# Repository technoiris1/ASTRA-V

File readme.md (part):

# ASTRA-V

heyo! Manan this side - this is my second big hardware project after my foldable 3d printer - ASTRA-V. Stands for Autonomous Stabilised Thrust Recovery Ascent Vehicle.<br>

The concept is simple - Go up - attain free fall - thrust again a lil when around 3 feet from the ground - land.

Its using LiDars to calculate the height precisely and they are pretty quick, so no problems.

First iteration -
This very iteration of ASTRA-V has the following tasks - going up 15 feet, attaining a proper stable freefall and then land. Now the word *land* is the main thing, so like this is what the hardest part is - so lets discuss the whole thing step by step.

## Launch
### Trigger
We are using a RF module to trigger the launch, it is in the flight controller.
### Process
The Servo motor will be kicked by the flight controller - which will open the flow of the O2 into the Acrylic Rod Chamber(We will come to the fuel part later on), and along with the servo - an arc ignitor will also be kicked which will burn the fuel. *sshhhhhhhhhhiiiiiiiiuuuuuuuuu* and with that the burnt fuel gases will come out pressurized of the nozzle and *shrrrooooommmm* the rockets up - it will go up 30 feet in this iteration.

## Free fall
Pretty simple, once reached the desired height(30 feet here) the valve will be kicked to close. Thus no oxidiser - thus no thrust and no more going up. Then it will just fall down - tearing down the vigilantly through the air.

## Landing
Now this is the special sauce, the complex thing - in simple words - LiDar sensors are highly sensitive sensors which mainly work on lasers so really quick. They will be sensing the altitude and sending it to the flight computer, now as soon as the altitude or around 15 feet (in this case) is reached - the computer will kick up the servo and ignitor once again to push enough thrust to neutralise the G force attained in the freefall. So like - the whole rocket will have a gentle touchdown in the air using thrusters. Now along with the engine mechanism, one more thing kicked would be the servo motors to deploy the landing legs - they have a really wide span as you can see in the images - so it gonna land really well.

## Flight Controller
Flight controller is a custom made from scratch which uses Pi pico as the main board. It uses MPU-6050 as the Gyro and BMP-280 as the altimeter as its a barometer. It has pins for breakouts of all these things along with connections with landing servos, LiDar sensors, Fuel Servos and the Arc Ignitor. It has 7 motor connections, 2 LiDar, 1 for MPU6050 and BMP280 each, it has different capacitors placed overall for fluctuations etc.

## Fuel
It is using Acrylic as a fuel along with O2 as the oxidiser. Pretty simple there is a chamber with acrylic rod and a servo controlled apparatus for the input of oxygen into the chamber. So the burnt O2 will heat up and burn the Acrylic rod, thus the Acrylic vapours will move out really really quickly off the nozzle providing thrust.

## Rocket motor and thrust vectoring
I am working on a basic servo controlled thrust vectoring system to control the direction of the thrust. This will allow for more precise control of the rocket's trajectory. The servos will be fitted on two different rings, one ring with a servo will be connected to the tube body of rocket and it will rotate another ring inside it, which is housing another servo and that servo will be connected to a ring joint to the rocket motor. So in this way there will be a whole 2-axis thrust vectoring system. I am currently working on the design and 3d model, will put here as soon as i'm done.

## Why am I making this thing?
cuz am crazy

## BOM
| ASTRA-V        | 1                                                                                                                                              | 2   |  3   | 4      |  5      |  6                                                                                                                                                                                                                                                                                                                                                                                                                                                                                                                                                                                                                                                                                                   |
|:----------------------|:--------------------------------------------------------------------------------------------------------------------------------------------------------|:-------------|:-------------|:----------------|:----------------|:-------------------------------------------------------------------------------------------------------------------------------------------------------------------------------------------------------------------------------------------------------------------------------------------------------------------------------------------------------------------------------------------------------------------------------------------------------------------------------------------------------------------------------------------------------------------------------------------------------------------------------------------------------------------------------------------------------------|
| ASTRA                 | Autonomous Stabilised Thrust Recovery Ascent                                                                                                            |              |              |                 |                 |                                                                                                                                                                                                                                                                                                                                                                                                                                                                                                                                                                                                                                                                                                              |
|                       |                                                                                                                                                         |              |              |                 |                 |                                                                                                                                                                                                                                                                                                                                                                                                                                                                                                                                                                                                                                                                                                              |
| BOM-                  |                                                                                                                                                         |              |              |                 |                 |                                                                                                                                                                                                                                                                                                                                                                                                                                                                                                                                                                                                                                                                                                              |
| Name                  | Use case                                                                                                                                                | price each   | units        | total price inr | total price usd | link                                                                                                                                                                                                                                                                                                                                                                                                                                                                                                                                                                                                                                                                                                         |
| MG946R servo motors   | Landing legs deployment                                                                                                                                 | 800          | 4            | 3200            | 37              | https://thinkrobotics.com/products/standard-metal-servo-mg946r-1?variant=12765401514056                                                                                                                                                                                                                                                                                                                                                                                                                                                                                                                                                                                                                      |
| LiDar sensor          | to measure height quickly                                                                                                                               | 2500         | 2            | 5000            | 57              | https://thinkrobotics.com/products/tf-luna-lidar-tof-distance-ranging-sensor-8m                                                                                                                                                                                                                                                                                                                                                                                                                                                                                                                                                                                                                              |
| Raspberry pi pico W   | the main controller of the flight                                                                                                                       | 700          | 2            | 1400            | 16              | https://thinkrobotics.com/products/raspberry-pi-pico-w-online?variant=44615124386109                                                                                                                                                                                                                                                                                                                                                                                                                                                                                                                                                                                                                         |
| BMP280 breakout       | the altimeter of the flight ctrl                                                                                                                        | 70           | 2            | 140             | 2               | https://thinkrobotics.com/products/bmp280-barometric-sensor-module-3-3v-5v?variant=32045116325974                                                                                                                                                                                                                                                                                                                                                                                                                                                                                                                                                                                                            |
| MPU 6050              | gyro sensor                                                                                                                                             | 300          | 2            | 600             | 7               | https://thinkrobotics.com/products/mpu6050-gyroscope-sensor?variant=16158094786632                                                                                                                                                                                                                                                                                                                                                                                                                                                                                                                                                                                                                           |
| nrf module            | trigger for rocket to go boom                                                                                                                           | 80           | 2            | 160             | 2               | https://roboticsdna.in/product/nrflongrenge24l01/                                                                                                                                                                                                                                                                                                                                                                                                                                                                                                                                                                                                                                                            |
| pin headers           | pin headers on pcb                                                                                                                                      | 11.5         | 20           | 250             | 3               | https://thinkrobotics.com/products/single-row-2-54-mm-pitch-header-40-pin?variant=12744266055752                                                                                                                                                                                                                                                                                                                                                                                                                                                                                                                                                                                                             |
| battery               | battery                                                                                                                                                 | 1900         | 1            | 1900            | 22              | https://robocraze.com/products/bonka-2200mah-35c-3s1p-11-1v-lipo-battey?_pos=1&_sid=bea5fbb80&_ss=r                                                                                                                                                                                                                                                                                                                                                                                                                                                                                                                                                                                                          |
| battery charger       | battery charger                                                                                                                                         | 350          | 1            | 350             | 4               | https://robocraze.com/products/b3-pro-li-po-battery-charger?_pos=2&_sid=bea5fbb80&_ss=r                                                                                                                                                                                                                                                                                                                                                                                                                                                                                                                                                                                                                      |
| 12v to 5v stepdown    | as the name suggests, its the best i could find right now as i need >15A to feed to all the servos and lidars and all, gonna use a simpler one if found | 1300         | 1            | 1300            | 15              | https://www.amazon.in/Regulator-Converter-Step-Down-Waterproof-Transformer/dp/B0BB7TNNR9/ref=sr_1_2?adgrpid=152001381314&dib=eyJ2IjoiMSJ9.7LdIaw4uy4t_ud4_Gg2x1FYfv0hCAr6r5n_X9XjOV1DIgPk0lzrRwCeS5vQJs9ifIwk5jeHmpClpv-KxfE_R6W-4eQ8La3mx5k82_zUEXtoWDIm8fWkmIPpgv6_Jc1wZnojyiQzVQ-MZeZGr-iGJw1jx3eatirHtnHmqE5kdzw5dZ7hAgFZO8xEtYhY6lZw5g143_Y3Bxg3XxFJVMQ1qbN5F_TIHW0vvLTUpqolevq4.H1BIrdzZZDv5Qg4POX_tB1USdrkHpUucbGJxVSRyHRA&dib_tag=se&ext_vrnc=hi&hvadid=658161935919&hvdev=c&hvlocphy=9061777&hvnetw=g&hvqmt=e&hvrand=16993244603842095821&hvtargid=kwd-332476321330&hydadcr=18599_2250683&keywords=12v%2Bto%2B5v%2Bconverter%2B10a&mcid=59e334a8862a3bdfa27f93f5b047b91e&qid=1757371930&sr=8-2&th=1 |
| 0.1uf ceramic cap     | on pcb                                                                                                                                                  | 5            | 3            | 15              | 1               | https://quartzcomponents.com/products/10000-pf-0-1uf-ceramic-capacitor?_pos=1&_sid=c9f6e0456&_ss=r                                                                                                                                                                                                                                                                                                                                                                                                                                                                                                                                                                                                           |
| 470uf cap             | on pcb                                                                                                                                                  | 7            | 3            | 21              | 1               | https://quartzcomponents.com/products/470uf-50v-electrolytic-capacitor?_pos=1&_sid=1ae57eeec&_ss=r                                                                                                                                                                                                                                                                                                                                                                                                                                                                                                                                                                                                           |
| 100uf cap             | on pcb                                                                                                                                                  | 3            | 10           | 30              | 1               | https://quartzcomponents.com/products/100%CE%BCf-35v-radial-electrolytic-capacitor?_pos=3&_sid=f5c2847a1&_ss=r                                                                                                                                                                                                                                                                                                                                                                                                                                                                                                                                                                                               |
| 10uf cap              | on pcb                                                                                                                                                  | 3            | 10           | 30              | 1               | https://quartzcomponents.com/products/10uf-50v-electrolytic-capacitor?_pos=2&_sid=5efdc15a5&_ss=r                                                                                                                                                                                                                                                                                                                                                                                                                                                                                                                                                                                                            |
| push button           | to be on the fire remote and some other usecases like replacing the arc ignitor small button with large ones to make it easier to work with             | 20           | 3            | 60              | 1               | https://thinkrobotics.com/products/6mm-tactile-push-button-pack-of-20?variant=33484370313302                                                                                                                                                                                                                                                                                                                                                                                                                                                                                                                                                                                                                 |
| arc igniter           | lighter for the fuel etc.                                                                                                                               | 150          | 2            | 300             | 4               | https://quartzcomponents.com/products/arc-cigarette-lighter-parts-diy-electronic-lighter-kit?variant=35137047789721&country=IN&currency=INR&utm_medium=product_sync&utm_source=google&utm_content=sag_organic&utm_campaign=sag_organic?utm_source=google&utm_medium=FreeListings&gad_source=1&gad_campaignid=20393598841&gbraid=0AAAAACPPFdPr-dR7QR1-p34kLl_MJcUyZ&gclid=CjwKCAjw2vTFBhAuEiwAFaScwrnDlRlH-qV1CVbSip1f13rZR5dapHQqdkiod5_ZJnDHndvW4T8w7hoCpK8QAvD_BwE                                                                                                                                                                                                                                         |
| 18650 li-on battery   | battery for the arc igniter                                                                                                                             | 100          | 2            | 200             | 3               |                                                                                                                                                                                                                                                                                                                                                                                                                                                                                                                                                                                                                                                                                                              |
| 18650 battery charger | charger for the battery                                                                                                                                 | 100          | 1            | 100             | 2               | https://quartzcomponents.com/products/18650-li-ion-battery-charger-for-single-cell?_pos=2&_sid=500a0bb39&_ss=r                                                                                                                                                                                                                                                                                                                                                                                                                                                                                                                                                                                               |
| 18650 battery holder  | holder for the battery                                                                                                                                  | 25           | 1            | 25              | 1               | https://quartzcomponents.com/products/single-cell-18650-li-ion-battery-holder?_pos=1&_sid=1d517396f&_ss=r                                                                                                                                                                                                                                                                                                                                                                                                                                                                                                                                                                                                    |
| flight controller PCB | main board                                                                                                                                              | 5000         | 1            | 5000            | 57              | https://github.com/Manan-Coder/ASTRA-V/tree/main/Flight%20Controller                                                                                                                                                                                                                                                                                                                                                                                                                                                                                                                                                                                                                                         |
| cardboard tube        | for the main tube, it will be having the glass cloth on it                                                                                              | 675          | 1            | 675             | 8               | https://www.amazon.in/Inches-Mailing-Tubes-Metal-Length/dp/B0CPWVSQKS/ref=sxin_15_pa_sp_search_thematic_sspa?content-id=amzn1.sym.739e670d-dfb3-4be0-9815-d8c5c0372e07%3Aamzn1.sym.739e670d-dfb3-4be0-9815-d8c5c0372e07&crid=2GBA8S78DLCM5&cv_ct_cx=cardboard%2Btube%2B4%22&keywords=cardboard%2Btube%2B4%22&pd_rd_i=B0CPWWGCS6&pd_rd_r=d6a15d33-a3c1-48d5-9d6b-41144c98fbc2&pd_rd_w=gimTs&pd_rd_wg=ga18o&pf_rd_p=739e670d-dfb3-4be0-9815-d8c5c0372e07&pf_rd_r=P861P04YA3F2CMA1501D&qid=1757196703&sbo=RZvfv%2F%2FHxDF%2BO5021pAnSA%3D%3D&sprefix=cardboard%2Btube%2B4%2Caps%2C326&sr=1-5-66673dcf-083f-43ba-b782-d4a436cc5cfb-spons&sp_csd=d2lkZ2V0TmFtZT1zcF9zZWFyY2hfdGhlbWF0aWM&th=1                     |
| fibre glass cloth     | to make the main tube and make it durable                                                                                                               | 650          | 1            | 650             | 8               | https://www.amazon.in/Fiber-Glass-Cloth-Thickness-10/dp/B0CX1W4TBQ/ref=sr_1_9?crid=1LLKHFYFT24HK&dib=eyJ2IjoiMSJ9.MnhabvxjPrKqUa-3qfa9HY03oFXYKF32Fj4yScgtEWZmGd4QetX8xCNmP-U4g03CMz332kFSD_Zr26WBeGN7ZlPdfwIAevGNnYGiaCj0NQtCt4dzZedN31q90f6f_DtvvAzWLvAysMYQN5fd6bhTNXrjic6mWXOIXJJkzA1OrG0wGstpOiyJcR-gjvNRUQdOQDPHR4tG6MCcP1jrJ2SmAj6i-Q2AUSvXU3IjdhgtvNQo_Au578cT7GSHlRpyLHSAwl6DbeVC0NJLR6-jL2DYqQsgoUJnBfwzdOTwIzhMt-U.9NS5zXLIkieWGsWLpckPP25cPN2hKeon7ZWg-9ju_l8&dib_tag=se&keywords=fibre+glass+cloth&qid=1757106200&sprefix=fibre+glass+clot%2Caps%2C308&sr=8-9                                                                                                                                   |
| epoxy resin           | to stick the glass cloth to the main tube                                                                                                               | 500          | 1            | 500             | 6               | https://www.amazon.in/gp/product/B0F5W94NLF/ref=ewc_pr_img_1?th=1                                                                                                                                                                                                                                                                                                                                                                                                                                                                                                                                                                                                                                            |
| Carbon Fibre rods     | Landing legs                                                                                                                                            | 140          | 12           | 1680            | 20              | https://thinkrobotics.com/products/carbon-fiber-solid-tube-1-m?variant=39329659650134                                                                                                                                                                                                                                                                                                                                                                                                                                                                                                                                                                                                                        |
| oxygen can            | oxidiser for fuel                                                                                                                                       | 1300         | 1            | 1300            | 15              | https://www.amazon.in/breathing-difficulties-Respiration-Lightweight-Travel-Friendly/dp/B0DNXRSX7V/ref=sr_1_5?crid=1GLANMNZO4DFP&dib=eyJ2IjoiMSJ9.2r-hUIMRfcgu623xclaCpK_-iEC730gRlXmkWliNUGdt0qy5bULYgXonakf4B36Uh0WasSftxzVFPrNAktj2EVcn-2fMG8zpUV9mtXioBG0G9hnYFOc7-LZp1YGxAK6olLUZcGkyajMMYhokfJNw9zN5ZWtMwgXmPMCdlI1JL_eUfaSdkcppavi69NRxH8qf2R-S3kvy6XL8fIAAZM1yUXyjKQ2K8U0sZQZjsODA-yz7ezUquskbvtoRdHeQGhA2eXAG0rphD2boIhf44l1VGK-8ra0dL3U5kXBO24t2_aY.CEHg3cM3qwtRtrb76YARkooG1utjq0rcfmYZsG-IRE8&dib_tag=se&keywords=oxygen%2Bcanister&qid=1757368995&sprefix=oxygen%2Bcaniste%2Caps%2C280&sr=8-5&th=1                                                                                              |
| acrylic rod           | main fuel on which oxygen act as an oxidiser                                                                                                            | 700          | 1            | 700             | 8               | https://www.amazon.in/Global-Plexiglass-Transparent-UV-Resistant-Diameter/dp/B07SR8LMRX/ref=sr_1_1?crid=2N9T65TDUGQ7L&dib=eyJ2IjoiMSJ9.UdoW_yhbRu-rPwuv5jEFcUYf1FEEFEn0SfLiBKnGdDes_OjLeSiOKAZ8YbriJ1hiybR8aLWx9DwmDxz_5RXnFkkPDVnbzKwKSQwV00rF356yCVtx4MlbsYAXd845hknkRTfE8GxFl3o_xlKQYH2QlOKYnYWvpFtkWpcfYkm-12g2K1wJNrUfN-eYaDZgszV_cuqD6769GquXxPoi0b3JsEhxxw3iyJ1gi8upuyJkLodE21gaUoEnJKd4jFkdbgOLcqjONI_RG7QA0yd-gzaKdJIhDfh0yRFjILQFA9-c9-Y.70e8miiM8udRYSD6PtKfP3KEIri9y9w0a85LdaNQ9LA&dib_tag=se&keywords=acrylic%2Brod%2Bindustrial&qid=1757369376&sprefix=acrylic%2Brod%2Bindustri%2Caps%2C260&sr=8-1&th=1                                                                                        |
| tube clamps           | clamps for the tube carrying oxygen to the chamber                                                                                                      | 160          | 1            | 160             | 2               | https://www.amazon.in/kitchenware-Store-clamp-pipe-safety/dp/B096NPHQLF/ref=sxin_15_pa_sp_search_thematic_sspa?content-id=amzn1.sym.739e670d-dfb3-4be0-9815-d8c5c0372e07%3Aamzn1.sym.739e670d-dfb3-4be0-9815-d8c5c0372e07&crid=2NONVX4WPA5NV&cv_ct_cx=gas+tube+small&keywords=gas+tube+small&pd_rd_i=B096NPHQLF&pd_rd_r=987b8181-6ae4-4506-bed4-0e67021a8e16&pd_rd_w=voQjF&pd_rd_wg=lcj1e&pf_rd_p=739e670d-dfb3-4be0-9815-d8c5c0372e07&pf_rd_r=PNNBZWY32FZP1K6JEPQ6&qid=1757370262&sbo=RZvfv%2F%2FHxDF%2BO5021pAnSA%3D%3D&sprefix=gas+tube+sma%2Caps%2C259&sr=1-1-66673dcf-083f-43ba-b782-d4a436cc5cfb-spons&sp_csd=d2lkZ2V0TmFtZT1zcF9zZWFyY2hfdGhlbWF0aWM&psc=1                                            |
| oxygen tube           | the tube which will carry the oxygen to the chamber                                                                                                     | 200          | 2            | 400             | 5               | https://www.amazon.in/ALEXERA-Mediplus-Oxygen-Tube-Length/dp/B0DDH3J4RS/ref=sr_1_7?dib=eyJ2IjoiMSJ9.Ip8quU3xBmwalpmXg4gcO6e2s-9j-0SCt-sJmqDscdDcawvS_A_C5AVmDei4NnTlKU18oGdAuJ0E0L41CSzVaGo9FVehx3To7FtboCR-DmVc9uSuibr9rDcgNffqd9_SFZNoB2DB9PN0oEZgPbj6S-LXwY7HmdPsc_w8Lc-iTUNrJPtiEOyOgcVo-ZARQtb2t37K26x0sKOG_DI6lxbQGCZxLFfeDXzjUzqB3RN62X6_OfGtEAUbOA6m0Nz_DbkS2CyvU7vh51Nr92FJUeYdMBIGBHiBEyLkJ55Q1pWrRi0.XgiwvfR9W-Z68orEphCs-NxjUQeToUYkcGqGQdfsf-M&dib_tag=se&keywords=tube+for+oxygen&qid=1757370438&sr=8-7                                                                                                                                                                                        |
| aluminium tube        | it will be the body of the rocket motor, the whole outer casing for safety and all that stuff                                                           | 1500         | 1            | 1500            | 18              | https://www.amazon.in/uxcell-Aluminum-Length-Seamless-Straight/dp/B083S6BKBW/ref=sr_1_7?crid=2K1BMUHLN6HFO&dib=eyJ2IjoiMSJ9.2g_FKttGy-3Nwo2jBrLaOzroA1LKsf7B8cKMbYsGZNa2cxip8LnD4v222xcz9UVG2SPPw8rRhPttkdmdiufH9bBA6JpXjeCHsciBmTKaO_GsWienEuVwlwwJA6eCSRjkCeryUsBHheDvAmDPcrAT0Oe9_b4ikyMgNKE5etjHk3oxHiv_NG06GZpgNb8usZHH1gM7HvEhgBR7-ftWSD2g78-hsXeEOpNMr3NwjA0Wf4W6_XfpInt9bq9863l90efAJqdSjOOZqDbxQA-Z0qs04rsCbSUCOAXzxg51R-MdEDA.CUC4a9pmQadY-sudgswJnI_IKUb1xPjoT-IgpqoiEOc&dib_tag=se&keywords=30mm%2Bod%2Baluminium%2Btube&qid=1757370924&sprefix=30mm%2Bod%2Baluminium%2Btub%2Caps%2C267&sr=8-7&th=1                                                                                              |
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
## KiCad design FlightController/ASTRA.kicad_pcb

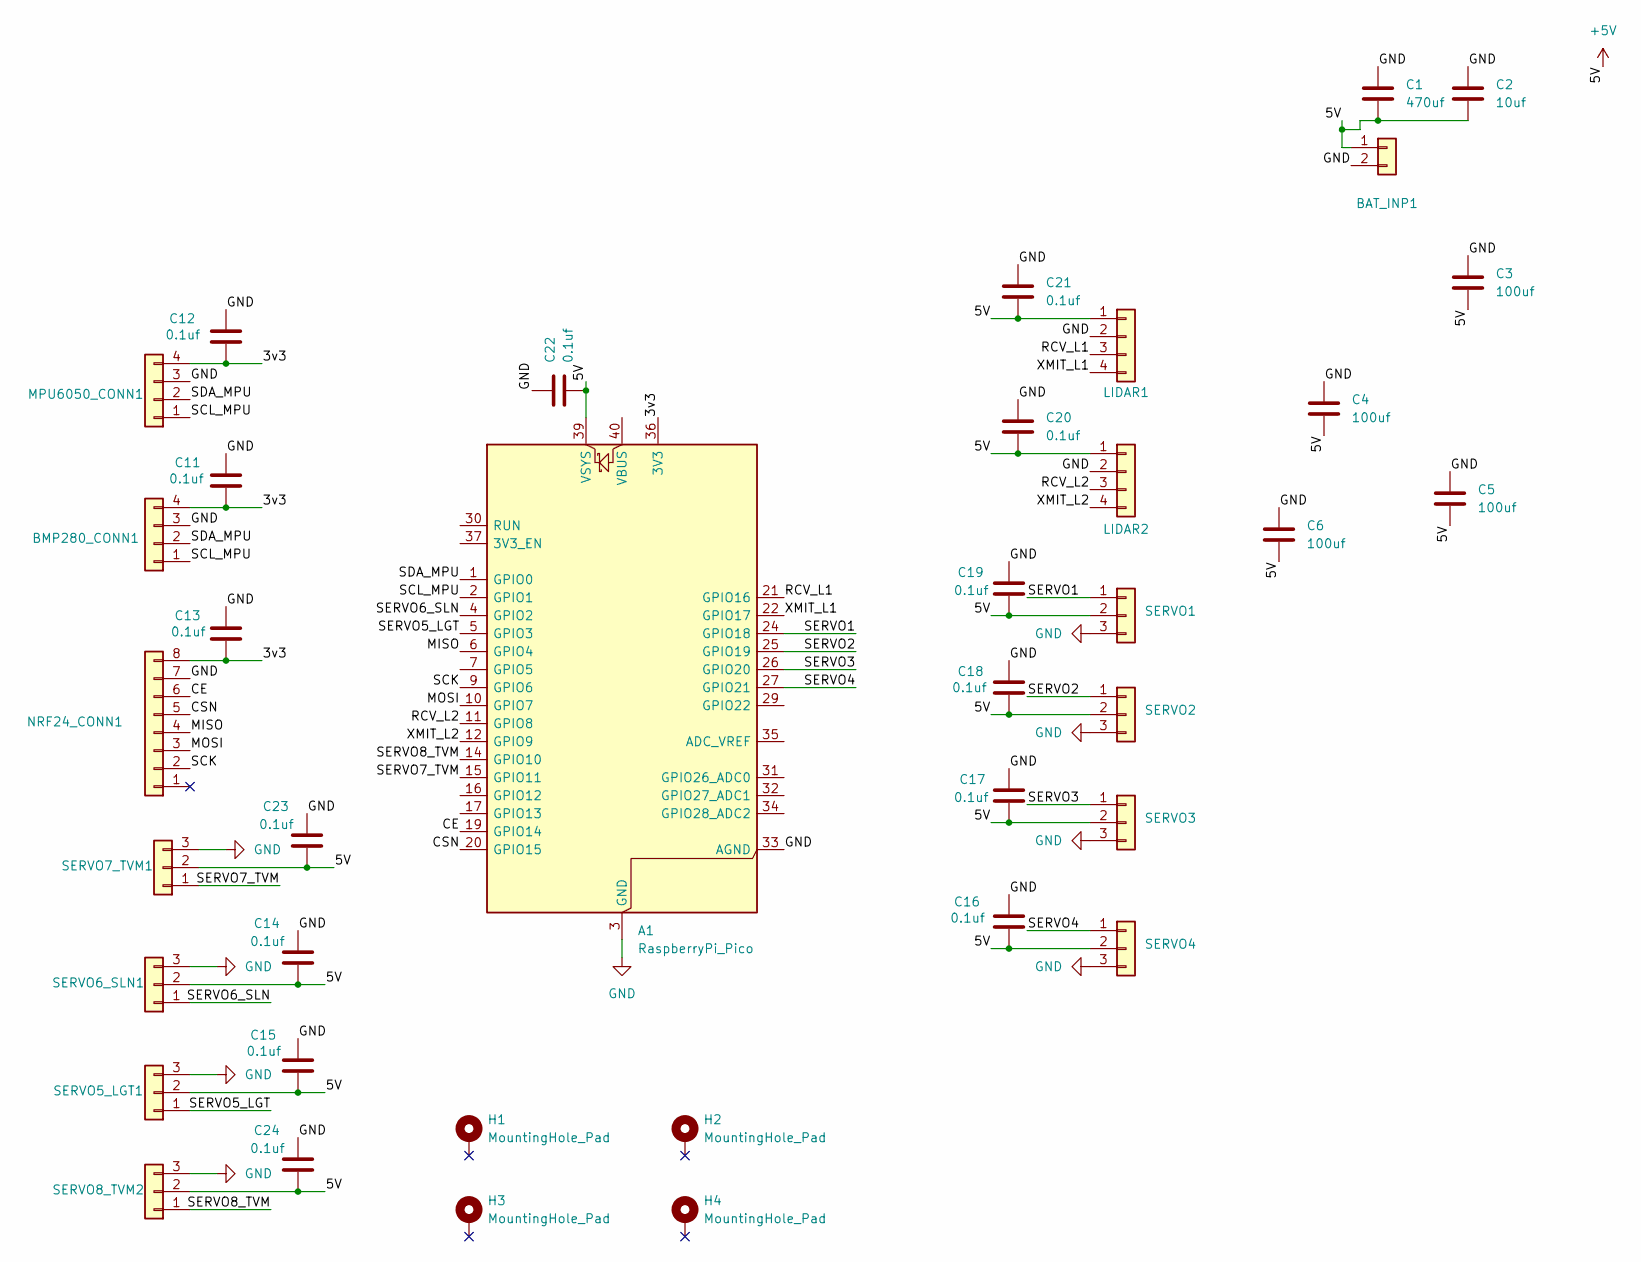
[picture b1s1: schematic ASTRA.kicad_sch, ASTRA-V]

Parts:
A1: RaspberryPi_Pico; RaspberryPi_Pico_Common_Unspecified
BAT_INP1: TerminalBlock_bornier-2_P5.08mm
BMP280_CONN1: PinHeader_1x04_P2.54mm_Vertical
C1: 470uf; CP_Radial_D10.0mm_P5.00mm
C2: 10uf; CP_Radial_D5.0mm_P2.00mm
C3, C4, C5, C6: 100uf; CP_Radial_D6.3mm_P2.50mm
C11, C12, C13, C14, C15, C16, C17, C18, C19, C20, C21, C22, C23, C24: 0.1uf; C_Disc_D3.0mm_W1.6mm_P2.50mm
H1, H2, H3, H4: MountingHole_Pad; MountingHole_2.2mm_M2_Pad_Via
LIDAR1, LIDAR2: PinHeader_1x04_P2.54mm_Vertical
MPU6050_CONN1: PinHeader_1x04_P2.54mm_Vertical
NRF24_CONN1: PinHeader_1x08_P2.54mm_Vertical
SERVO1, SERVO2, SERVO3, SERVO4, SERVO5_LGT1, SERVO6_SLN1, SERVO7_TVM1, SERVO8_TVM2: PinHeader_1x03_P2.54mm_Vertical

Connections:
/3v3: A1.36 (3V3), BMP280_CONN1.4, C11.2, C12.2, C13.2, MPU6050_CONN1.4, NRF24_CONN1.8
/5V: A1.39 (VSYS), BAT_INP1.1, C1.1, C2.1, C3.1, C4.1, C5.1, C6.1, C14.2, C15.2, C16.2, C17.2, C18.2, C19.2, C20.2, C21.2, C22.2, C23.2, C24.2, LIDAR1.1, LIDAR2.1, SERVO1.2, SERVO2.2, SERVO3.2, SERVO4.2, SERVO5_LGT1.2, SERVO6_SLN1.2, SERVO7_TVM1.2, SERVO8_TVM2.2
/CE: A1.19 (GPIO14), NRF24_CONN1.6
/CSN: A1.20 (GPIO15), NRF24_CONN1.5
/MISO: A1.6 (GPIO4), NRF24_CONN1.4
/MOSI: A1.10 (GPIO7), NRF24_CONN1.3
/RCV_L1: A1.21 (GPIO16), LIDAR1.3
/RCV_L2: A1.11 (GPIO8), LIDAR2.3
/SCK: A1.9 (GPIO6), NRF24_CONN1.2
/SCL_MPU: A1.2 (GPIO1), BMP280_CONN1.1, MPU6050_CONN1.1
/SDA_MPU: A1.1 (GPIO0), BMP280_CONN1.2, MPU6050_CONN1.2
/SERVO1: A1.24 (GPIO18), SERVO1.1
/SERVO2: A1.25 (GPIO19), SERVO2.1
/SERVO3: A1.26 (GPIO20), SERVO3.1
/SERVO4: A1.27 (GPIO21), SERVO4.1
/SERVO5_LGT: A1.5 (GPIO3), SERVO5_LGT1.1
/SERVO6_SLN: A1.4 (GPIO2), SERVO6_SLN1.1
/SERVO7_TVM: A1.15 (GPIO11), SERVO7_TVM1.1
/SERVO8_TVM: A1.14 (GPIO10), SERVO8_TVM2.1
/XMIT_L1: A1.22 (GPIO17), LIDAR1.4
/XMIT_L2: A1.12 (GPIO9), LIDAR2.4
GND: A1.3 (GND), A1.8 (GND), A1.13 (GND), A1.18 (GND), A1.23 (GND), A1.28 (GND), A1.33 (AGND), A1.38 (GND), BAT_INP1.2, BMP280_CONN1.3, C1.2, C2.2, C3.2, C4.2, C5.2, C6.2, C11.1, C12.1, C13.1, C14.1, C15.1, C16.1, C17.1, C18.1, C19.1, C20.1, C21.1, C22.1, C23.1, C24.1, LIDAR1.2, LIDAR2.2, MPU6050_CONN1.3, NRF24_CONN1.7, SERVO1.3, SERVO2.3, SERVO3.3, SERVO4.3, SERVO5_LGT1.3, SERVO6_SLN1.3, SERVO7_TVM1.3, SERVO8_TVM2.3

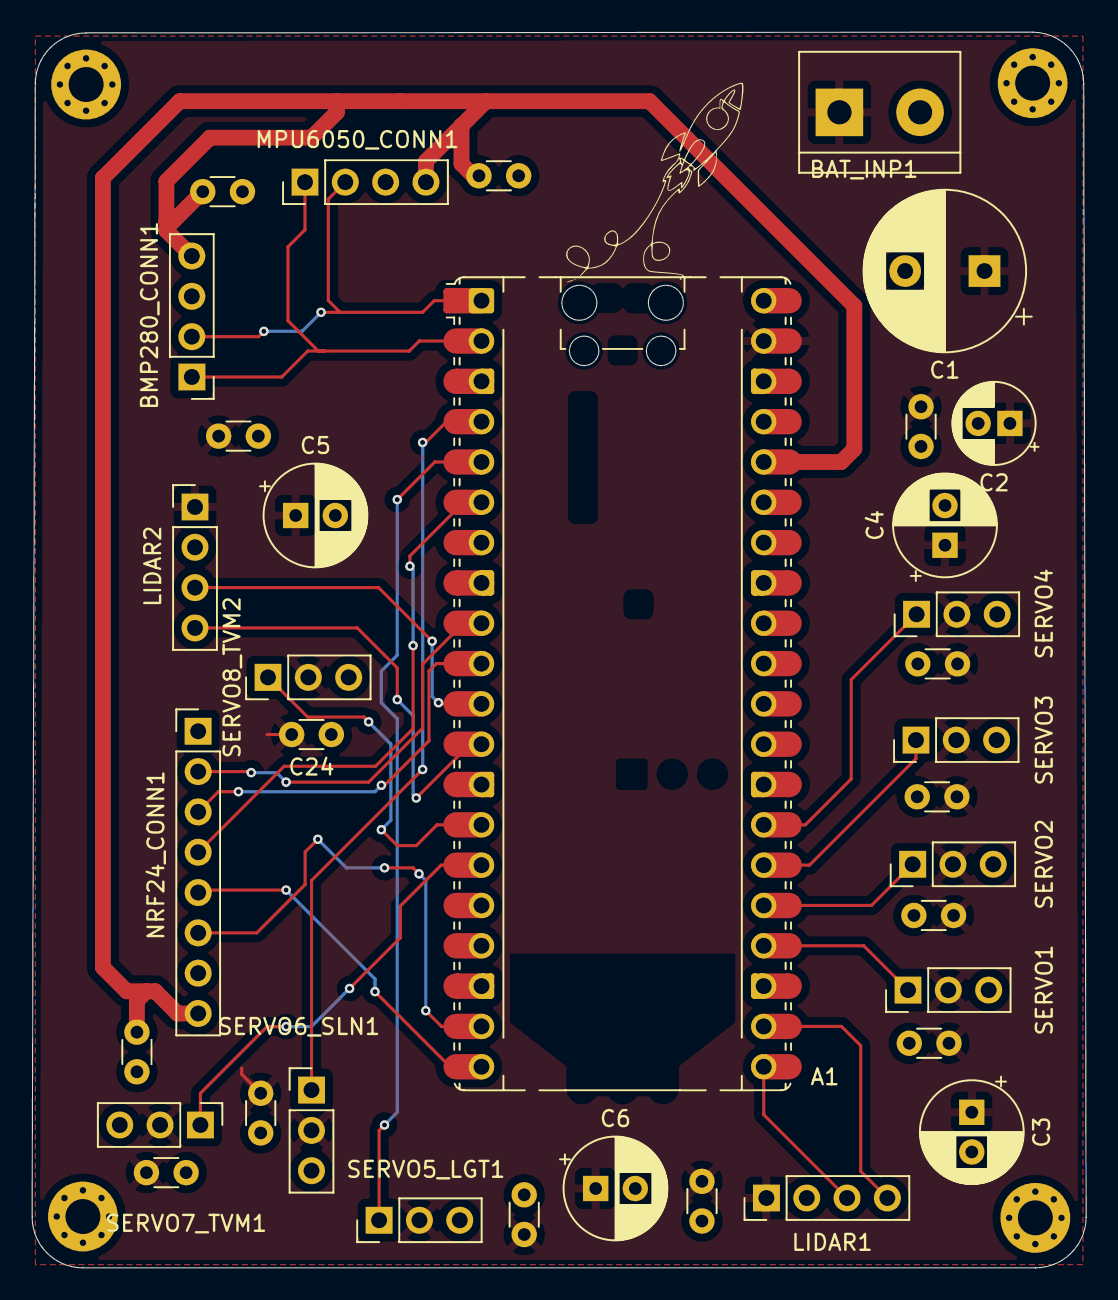
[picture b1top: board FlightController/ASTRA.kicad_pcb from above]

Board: 2 copper layers, 66.4 x 77.8 mm, 39 parts (0 on the bottom side), 22 nets.

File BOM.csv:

Manan Sharma,,,,,,
ASTRA,Autonomous Stabilised Thrust Recovery Ascent,,,,,
,,,,,,
BOM-,,,,,,
Name,Use case,price each,units,total price inr,total price usd,link
MG946R servo motors, Landing legs deployment,800,4,3200,37,https://thinkrobotics.com/products/standard-metal-servo-mg94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
LiDar sensor,to measure height quickly,2500,2,5000,57,https://thinkrobotics.com/products/tf-luna-lidar-tof-distanc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
Raspberry pi pico W,the main controller of the flight,700,2,1400,16,https://thinkrobotics.com/products/raspberry-pi-pico-w-onlin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
BMP280 breakout,the altimeter of the flight ctrl,70,2,140,2,https://thinkrobotics.com/products/bmp280-barometric-sensor-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
MPU 6050,gyro sensor,300,2,600,7,https://thinkrobotics.com/products/mpu6050-gyroscope-sensor?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
nrf module,trigger for rocket to go boom,80,2,160,2,https://roboticsdna.in/product/nrflongrenge24l01/
pin headers,pin headers on pcb,11.5,20,250,3,https://thinkrobotics.com/products/single-row-2-54-mm-pitch-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
battery,battery ,1900,1,1900,22,https://robocraze.com/products/bonka-2200mah-35c-3s1p-11-1v-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
battery charger,battery charger,350,1,350,4,https://robocraze.com/products/b3-pro-li-po-battery-charger?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
12v to 5v stepdown,"as the name suggests, its the best i could find right now as i need >15A to feed to all the servos and lidars and all, gonna use a simpler one if found",1300,1,1300,15,https://www.amazon.in/Regulator-Converter-Step-Down-Waterpro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
0.1uf ceramic cap,on pcb,5,3,15,1,https://quartzcomponents.com/products/10000-pf-0-1uf-ceramic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
470uf cap,on pcb,7,3,21,1,https://quartzcomponents.com/products/470uf-50v-electrolytic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
100uf cap,on pcb,3,10,30,1,https://quartzcomponents.com/products/100%CE%BCf-35v-radial-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
10uf cap,on pcb,3,10,30,1,https://quartzcomponents.com/products/10uf-50v-electrolytic-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
push button,to be on the fire remote and some other usecases like replacing the arc ignitor small button with large ones to make it easier to work with,20,3,60,1,https://thinkrobotics.com/products/6mm-tactile-push-button-p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
arc igniter,lighter for the fuel etc.,150,2,300,4,https://quartzcomponents.com/products/arc-cigarette-lighter-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
18650 li-on battery,battery for the arc igniter,100,2,200,3,
18650 battery charger,charger for the battery,100,1,100,2,https://quartzcomponents.com/products/18650-li-ion-battery-c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
18650 battery holder,holder for the battery,25,1,25,1,https://quartzcomponents.com/products/single-cell-18650-li-i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
flight controller PCB,main board,5000,1,5000,57,https://github.com/Manan-Coder/ASTRA-V/tree/main/Flight%20Co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
cardboard tube,"for the main tube, it will be having the glass cloth on it",675,1,675,8,https://www.amazon.in/Inches-Mailing-Tubes-Metal-Length/dp/B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
fibre glass cloth,to make the main tube and make it durable,650,1,650,8,https://www.amazon.in/Fiber-Glass-Cloth-Thickness-10/dp/B0CX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
epoxy resin,to stick the glass cloth to the main tube,500,1,500,6,https://www.amazon.in/gp/product/B0F5W94NLF/ref=ewc_pr_img_1?th=1
Carbon Fibre rods,Landing legs,140,12,1680,20,https://thinkrobotics.com/products/carbon-fiber-solid-tube-1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
oxygen can,oxidiser for fuel,1300,1,1300,15,https://www.amazon.in/breathing-difficulties-Respiration-Lig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
acrylic rod,main fuel on which oxygen act as an oxidiser,700,1,700,8,https://www.amazon.in/Global-Plexiglass-Transparent-UV-Resis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
tube clamps,clamps for the tube carrying oxygen to the chamber,160,1,160,2,https://www.amazon.in/kitchenware-Store-clamp-pipe-safety/dp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
oxygen tube,the tube which will carry the oxygen to the chamber,200,2,400,5,https://www.amazon.in/ALEXERA-Mediplus-Oxygen-Tube-Length/dp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
aluminium tube,"it will be the body of the rocket motor, the whole outer casing for safety and all that stuff",1500,1,1500,18,https://www.amazon.in/uxcell-Aluminum-Length-Seamless-Straig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
graphite plate,it will be cnc'ed to act as the nozzle,1300,1,1300,15,https://www.amazon.in/Graphite-Operation-Practical-Craftsman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
nozzle,to make the input of oxygen clean and safe,450,1,450,6,https://www.amazon.in/Viking-Brass-Nozzle-Gas-Geysers/dp/B08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
,,,,,,
,,,,,,
,,,,,,
,,,total-,29396,348,

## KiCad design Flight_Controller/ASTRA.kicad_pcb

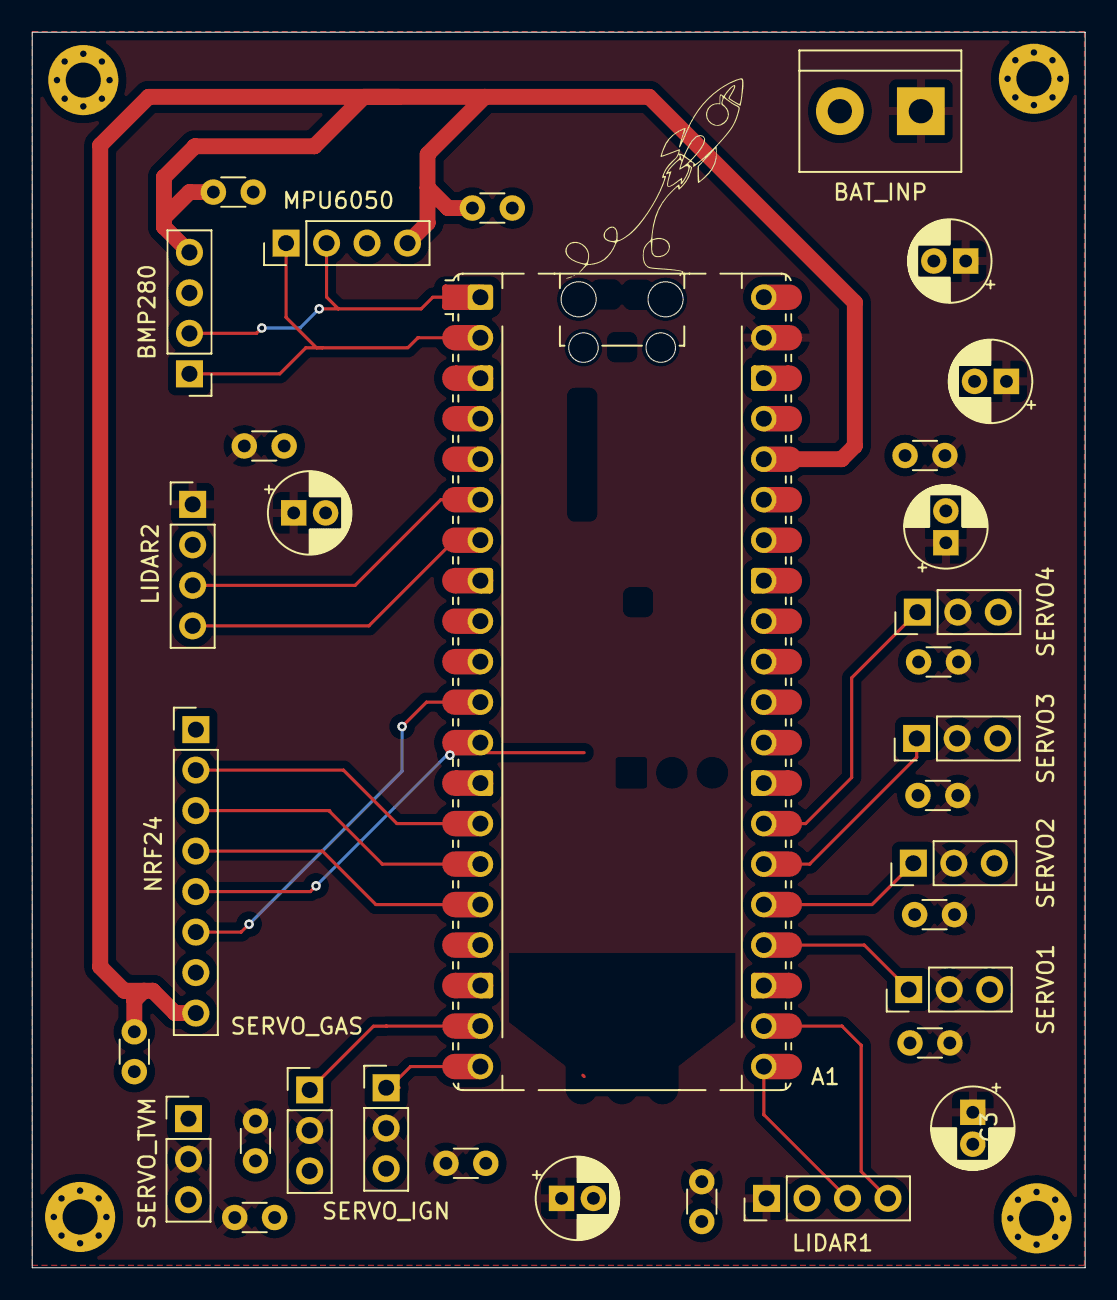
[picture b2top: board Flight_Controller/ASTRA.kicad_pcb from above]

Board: 2 copper layers, 66.0 x 77.5 mm, 37 parts (0 on the bottom side), 21 nets.

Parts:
A1: RaspberryPi_Pico; RaspberryPi_Pico_Common_Unspecified
BAT_INP: TerminalBlock_bornier-2_P5.08mm
BMP280: PinHeader_1x04_P2.54mm_Vertical
C1: 470uf; CP_Radial_D5.0mm_P2.00mm
C2: 10uf; CP_Radial_D5.0mm_P2.00mm
C3, C4, C4#2, C5: 100uf; CP_Radial_D5.0mm_P2.00mm
C11, C12, C13, C14, C15, C16, C17, C18, C19, C20, C21, C22, C23: 0.1uf; C_Disc_D3.0mm_W1.6mm_P2.50mm
H1, H2, H3, H4: MountingHole_Pad; MountingHole_2.2mm_M2_Pad_Via
LIDAR1, LIDAR2: PinHeader_1x04_P2.54mm_Vertical
MPU6050: PinHeader_1x04_P2.54mm_Vertical
NRF24: PinHeader_1x08_P2.54mm_Vertical
SERVO1, SERVO2, SERVO3, SERVO4: PinHeader_1x03_P2.54mm_Vertical
SERVO_GAS: PinHeader_1x03_P2.54mm_Vertical
SERVO_IGN: PinHeader_1x03_P2.54mm_Vertical
SERVO_TVM: PinHeader_1x03_P2.54mm_Vertical

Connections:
/3v3: A1.36 (3V3), BMP280.4, C11.2, C12.2, C13.2, MPU6050.4, NRF24.8
/5V: A1.39 (VSYS), BAT_INP.1, C1.1, C2.1, C3.1, C4.1, C4#2.1, C5.1, C14.2, C15.2, C16.2, C17.2, C18.2, C19.2, C20.2, C21.2, C22.2, C23.2, LIDAR1.1, LIDAR2.1, SERVO1.2, SERVO2.2, SERVO3.2, SERVO4.2, SERVO_GAS.2, SERVO_IGN.2, SERVO_TVM.2
/CE: A1.11 (GPIO8), NRF24.6
/CSN: A1.12 (GPIO9), NRF24.5
/MISO: A1.16 (GPIO12), NRF24.4
/MOSI: A1.15 (GPIO11), NRF24.3
/RCV_L1: A1.21 (GPIO16), LIDAR1.3
/RCV_L2: A1.6 (GPIO4), LIDAR2.3
/SCK: A1.14 (GPIO10), NRF24.2
/SCL_MPU: A1.2 (GPIO1), BMP280.1, MPU6050.1
/SDA_MPU: A1.1 (GPIO0), BMP280.2, MPU6050.2
/SERVO1: A1.24 (GPIO18), SERVO1.1
/SERVO2: A1.25 (GPIO19), SERVO2.1
/SERVO3: A1.26 (GPIO20), SERVO3.1
/SERVO4: A1.27 (GPIO21), SERVO4.1
/SERVO5_LGT: A1.20 (GPIO15), SERVO_IGN.1
/SERVO6_SLN: A1.19 (GPIO14), SERVO_GAS.1
/SERVO7_TVM: A1.10 (GPIO7), SERVO_TVM.1
/XMIT_L1: A1.22 (GPIO17), LIDAR1.4
/XMIT_L2: A1.7 (GPIO5), LIDAR2.4
GND: A1.3 (GND), A1.8 (GND), A1.13 (GND), A1.18 (GND), A1.23 (GND), A1.28 (GND), A1.33 (AGND), A1.38 (GND), BAT_INP.2, BMP280.3, C1.2, C2.2, C3.2, C4.2, C4#2.2, C5.2, C11.1, C12.1, C13.1, C14.1, C15.1, C16.1, C17.1, C18.1, C19.1, C20.1, C21.1, C22.1, C23.1, LIDAR1.2, LIDAR2.2, MPU6050.3, NRF24.7, SERVO1.3, SERVO2.3, SERVO3.3, SERVO4.3, SERVO_GAS.3, SERVO_IGN.3, SERVO_TVM.3

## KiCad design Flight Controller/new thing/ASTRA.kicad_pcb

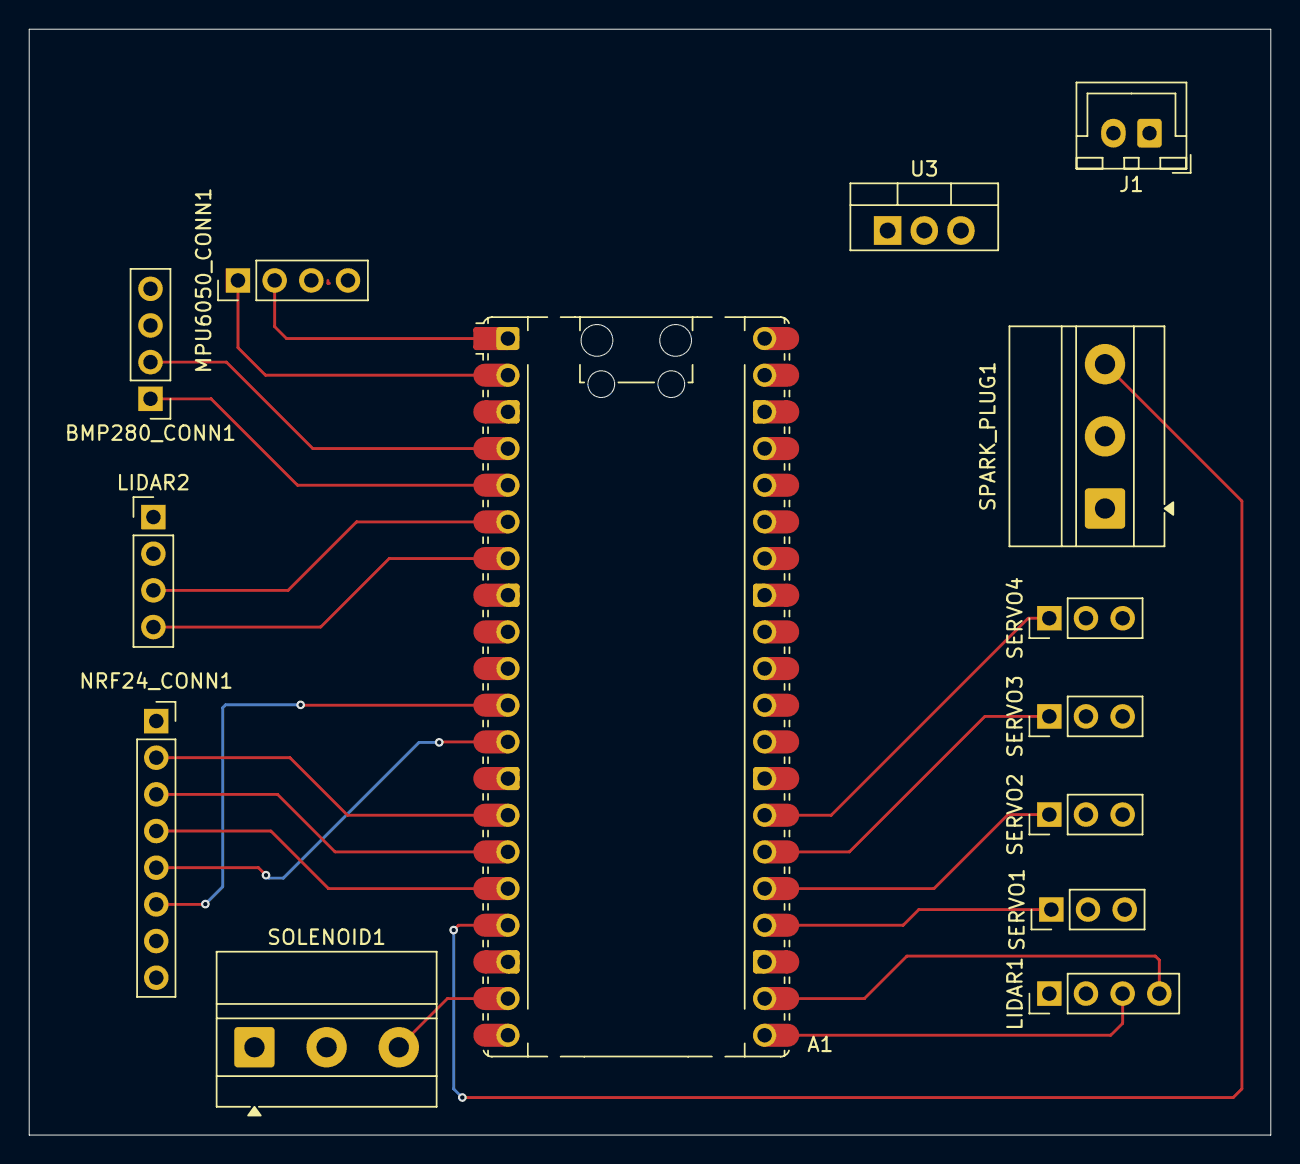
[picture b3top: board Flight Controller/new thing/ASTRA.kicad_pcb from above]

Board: 2 copper layers, 86.0 x 76.6 mm, 14 parts (0 on the bottom side), 22 nets.

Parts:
A1: RaspberryPi_Pico; RaspberryPi_Pico_Common_Unspecified
BMP280_CONN1: PinHeader_1x04_P2.54mm_Vertical
J1: BATTERY_IN; JST_XH_B2B-XH-A_1x02_P2.50mm_Vertical
LIDAR1, LIDAR2: PinHeader_1x04_P2.54mm_Vertical
MPU6050_CONN1: PinHeader_1x04_P2.54mm_Vertical
NRF24_CONN1: PinSocket_1x08_P2.54mm_Vertical
SERVO1, SERVO2, SERVO3, SERVO4: PinHeader_1x03_P2.54mm_Vertical
SOLENOID1: TerminalBlock_MetzConnect_Type011_RT05503HBLC_1x03_P5.00mm_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
SPARK_PLUG1: TerminalBlock_MetzConnect_Type011_RT05503HBLC_1x03_P5.00mm_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
U3: LM7805_TO220; TO-220-3_Vertical

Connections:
/CE: A1.11 (GPIO8), NRF24_CONN1.6
/CSN: A1.12 (GPIO9), NRF24_CONN1.5
/GPIO_NCH: A1.17 (GPIO13), SPARK_PLUG1.3
/GPIO_SLN: A1.29 (GPIO22), SOLENOID1.3
/MISO: A1.16 (GPIO12), NRF24_CONN1.4
/MOSI: A1.15 (GPIO11), NRF24_CONN1.3
/PWR: SOLENOID1.1, SPARK_PLUG1.1
/RCV_L1: A1.21 (GPIO16), LIDAR1.3
/RCV_L2: A1.6 (GPIO4), LIDAR2.3
/SCK: A1.14 (GPIO10), NRF24_CONN1.2
/SCL_BMP: A1.5 (GPIO3), BMP280_CONN1.1
/SCL_MPU: A1.2 (GPIO1), MPU6050_CONN1.1
/SDA_BMP: A1.4 (GPIO2), BMP280_CONN1.2
/SDA_MPU: A1.1 (GPIO0), MPU6050_CONN1.2
/SERVO1: A1.24 (GPIO18), SERVO1.1
/SERVO2: A1.25 (GPIO19), SERVO2.1
/SERVO3: A1.26 (GPIO20), SERVO3.1
/SERVO4: A1.27 (GPIO21), SERVO4.1
/XMIT_L1: A1.22 (GPIO17), LIDAR1.4
/XMIT_L2: A1.7 (GPIO5), LIDAR2.4
GND: A1.3 (GND), A1.8 (GND), A1.13 (GND), A1.18 (GND), A1.23 (GND), A1.28 (GND), A1.33 (AGND), A1.38 (GND), BMP280_CONN1.3, J1.1, LIDAR1.2, LIDAR2.2, MPU6050_CONN1.3, NRF24_CONN1.7, SERVO1.3, SERVO2.3, SERVO3.3, SERVO4.3, SOLENOID1.2, SPARK_PLUG1.2, U3.2 (GND)
VCC: A1.36 (3V3), BMP280_CONN1.4, J1.2, LIDAR1.1, LIDAR2.1, MPU6050_CONN1.4, NRF24_CONN1.8, U3.1 (VI)

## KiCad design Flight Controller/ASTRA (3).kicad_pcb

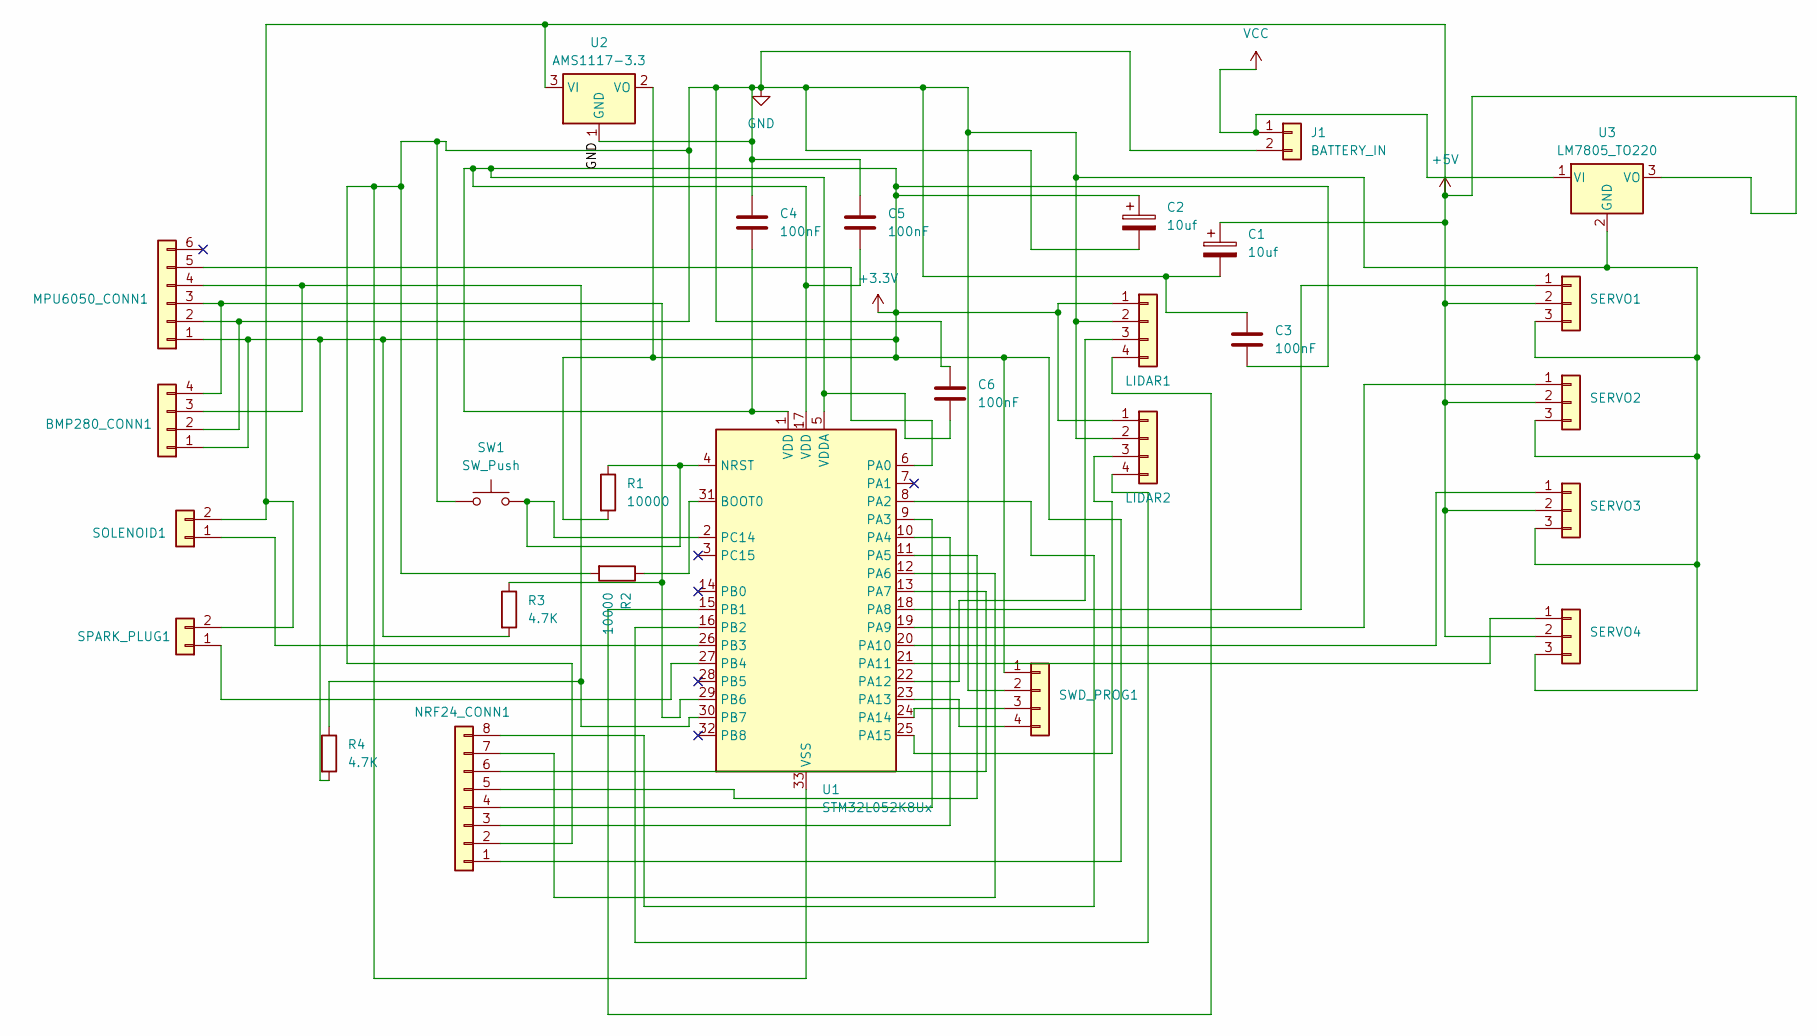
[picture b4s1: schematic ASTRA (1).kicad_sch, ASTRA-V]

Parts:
BMP280_CONN1: PinHeader_1x04_P2.54mm_Vertical
C1, C2: 10uf; CP_Radial_D8.0mm_P3.50mm
C3, C4, C5, C6: 100nF; C_Disc_D5.0mm_W2.5mm_P5.00mm
J1: BATTERY_IN; JST_XH_B2B-XH-A_1x02_P2.50mm_Vertical
LIDAR1, LIDAR2: PinHeader_1x04_P2.54mm_Vertical
MPU6050_CONN1: PinHeader_1x06_P2.54mm_Vertical
NRF24_CONN1: PinSocket_1x08_P2.54mm_Vertical
R1, R2: 10000; R_Axial_DIN0207_L6.3mm_D2.5mm_P10.16mm_Horizontal
R3, R4: 4.7K; R_Axial_DIN0207_L6.3mm_D2.5mm_P10.16mm_Horizontal
SERVO1, SERVO2, SERVO3, SERVO4: PinHeader_1x03_P2.54mm_Vertical
SOLENOID1: PinHeader_1x02_P2.54mm_Vertical
SPARK_PLUG1: PinHeader_1x02_P2.54mm_Vertical
SW1: SW_Push; SW_Push_2P1T_Toggle_CK_PVA1xxH4xxxxxxV2
SWD_PROG1: PinHeader_1x04_P2.54mm_Vertical
U1: STM32L052K8Ux; QFN-32-1EP_5x5mm_P0.5mm_EP3.45x3.45mm
U2: AMS1117-3.3; SOT-223-3_TabPin2
U3: LM7805_TO220; TO-220-3_Vertical

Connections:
+3.3V: BMP280_CONN1.1, C2.1, C3.2, C4.2, C5.2, C6.2, LIDAR1.1, LIDAR2.1, MPU6050_CONN1.1, NRF24_CONN1.1, R1.2, R3.2, R4.2, SWD_PROG1.1, U1.1 (VDD), U1.5 (VDDA), U1.17 (VDD), U2.2 (VO)
/GND: BMP280_CONN1.2, C1.2, C2.2, C3.1, C4.1, C5.1, C6.1, J1.2, LIDAR1.2, LIDAR2.2, MPU6050_CONN1.2, NRF24_CONN1.2, R2.2, SERVO1.3, SERVO2.3, SERVO3.3, SERVO4.3, SW1.1, SWD_PROG1.2, U1.33 (VSS), U2.1 (GND), U3.2 (GND)
unnamed: BMP280_CONN1.3, MPU6050_CONN1.4, R4.1, U1.30 (PB7)
unnamed: BMP280_CONN1.4, MPU6050_CONN1.3, R3.1, U1.29 (PB6)
unnamed: LIDAR1.3, U1.22 (PA12)
unnamed: LIDAR1.4, U1.15 (PB1)
unnamed: LIDAR2.3, U1.25 (PA15)
unnamed: LIDAR2.4, U1.16 (PB2)
unnamed: MPU6050_CONN1.5, U1.6 (PA0)
unnamed: NRF24_CONN1.3, U1.10 (PA4)
unnamed: NRF24_CONN1.4, U1.9 (PA3)
unnamed: NRF24_CONN1.5, U1.11 (PA5)
unnamed: NRF24_CONN1.6, U1.13 (PA7)
unnamed: NRF24_CONN1.7, U1.12 (PA6)
unnamed: NRF24_CONN1.8, U1.8 (PA2)
unnamed: SERVO1.1, U1.18 (PA8)
unnamed: C1.1, SERVO1.2, SERVO2.2, SERVO3.2, SERVO4.2, SOLENOID1.2, SPARK_PLUG1.2, U2.3 (VI), U3.3 (VO)
unnamed: SERVO2.1, U1.19 (PA9)
unnamed: SERVO3.1, U1.20 (PA10)
unnamed: SERVO4.1, U1.21 (PA11)
unnamed: SOLENOID1.1, U1.26 (PB3)
unnamed: SPARK_PLUG1.1, U1.27 (PB4)
unnamed: SWD_PROG1.3, U1.24 (PA14)
unnamed: SWD_PROG1.4, U1.23 (PA13)
unnamed: R2.1, U1.31 (BOOT0)
unnamed: R1.1, SW1.2, U1.2 (PC14), U1.4 (NRST)
VCC: J1.1, U3.1 (VI)

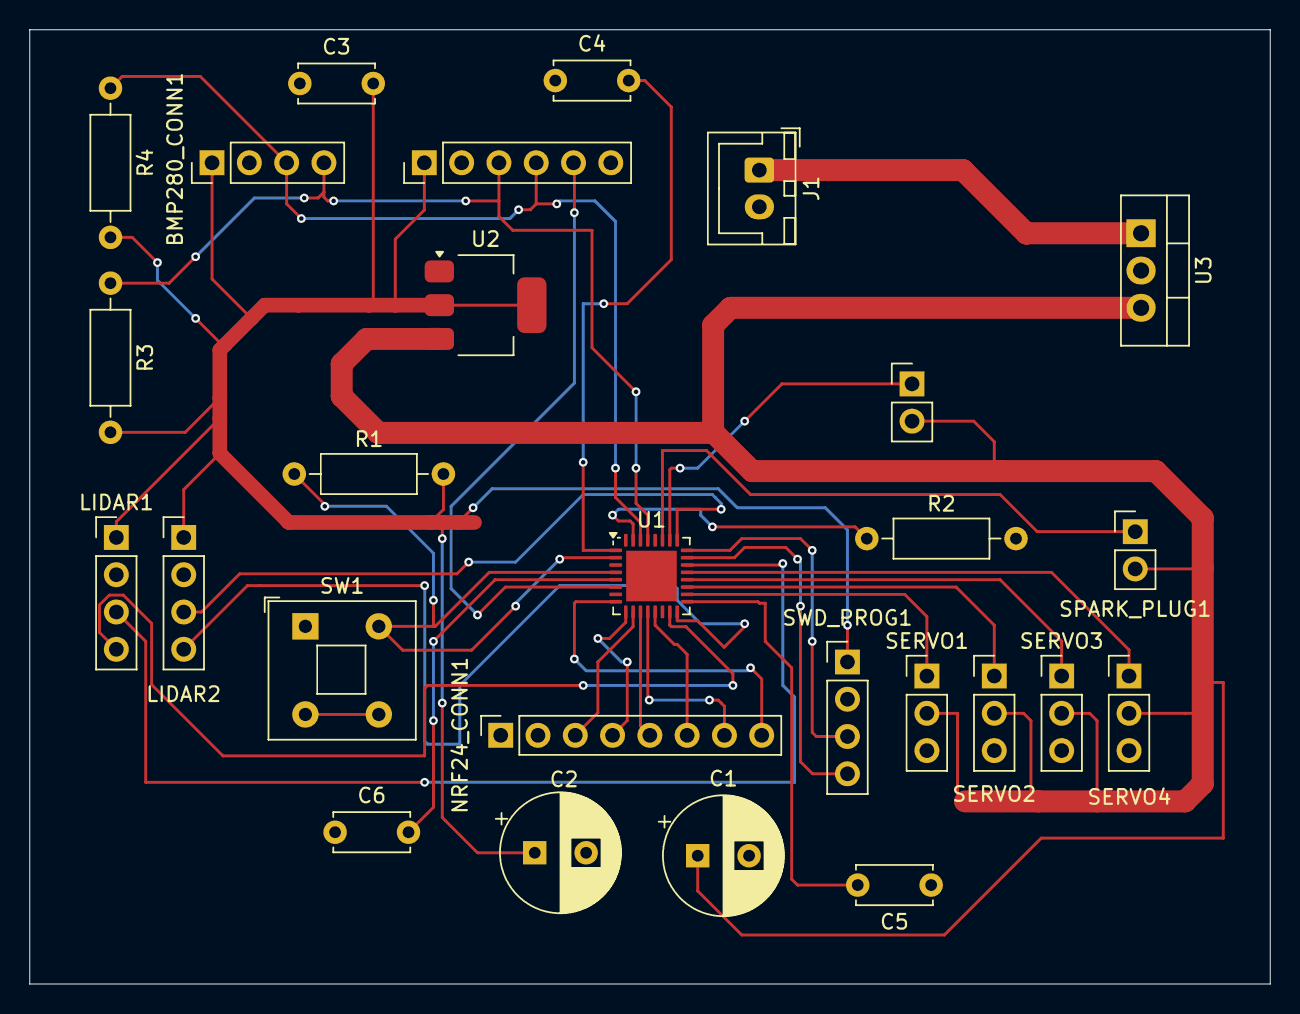
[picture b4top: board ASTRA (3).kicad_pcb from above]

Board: 2 copper layers, 84.5 x 65.0 mm, 27 parts (0 on the bottom side), 27 nets.

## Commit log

2025-07-14 initial set up
2025-07-14 day1 - 14th july
2025-07-15 day2 - 15th july
2025-07-15 added info
2025-07-15 added openrocket files
2025-07-15 added a body tube to simulate the leg ring
2025-07-17 made the body of the rocket in openrocket
2025-07-20 set up the motor config for simulations
2025-07-21 ran a few simulations and everything looks fine for now
    can proceed with the cad model
2025-07-29 29th july
2025-07-31 30th and 31st July
2025-07-31 added CAD
2025-07-31 30th july
2025-07-31 added schematics file
2025-07-31 added pcb
2025-07-31 added bom and readme
2025-07-31 added images of the cad
2025-08-01 updated the readme
2025-08-01 it did a lil funny
2025-08-07 august 1 and 6
2025-08-07 the current pcb files
2025-08-07 august 7th
2025-08-11 august 10th
2025-08-21 the new pcb
2025-09-01 added the proper .step and .f3d files
2025-09-01 readme update
2025-09-01 lil tweak
2025-09-04 some day
2025-09-06 added new pcb
2025-09-07 removed old files from tracking
2025-09-07 a lil tweak on the pcb
2025-09-07 updated bom
2025-09-07 update on time
2025-09-08 fixed the issue in the bom in readme and the csv
2025-09-08 the updated flight code
2025-09-08 trying to remove the .DS_Store file
2025-09-08 fixed an issue with the bom at both the places
2025-09-11 new improved pcb
2025-09-11 deleted previous pcb files
2025-09-11 lil tweaks
2025-09-12 removed previous files
2025-09-13 added pcb image to the readme
2026-01-16 new entry
2026-01-16 added new flight controller pcb files
2026-03-22 entry
